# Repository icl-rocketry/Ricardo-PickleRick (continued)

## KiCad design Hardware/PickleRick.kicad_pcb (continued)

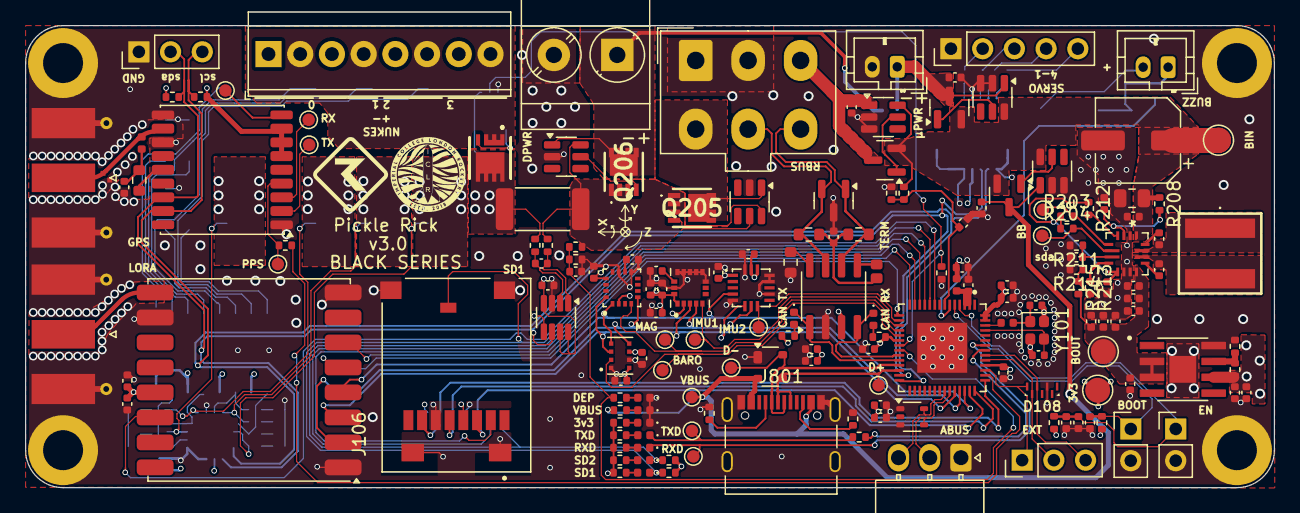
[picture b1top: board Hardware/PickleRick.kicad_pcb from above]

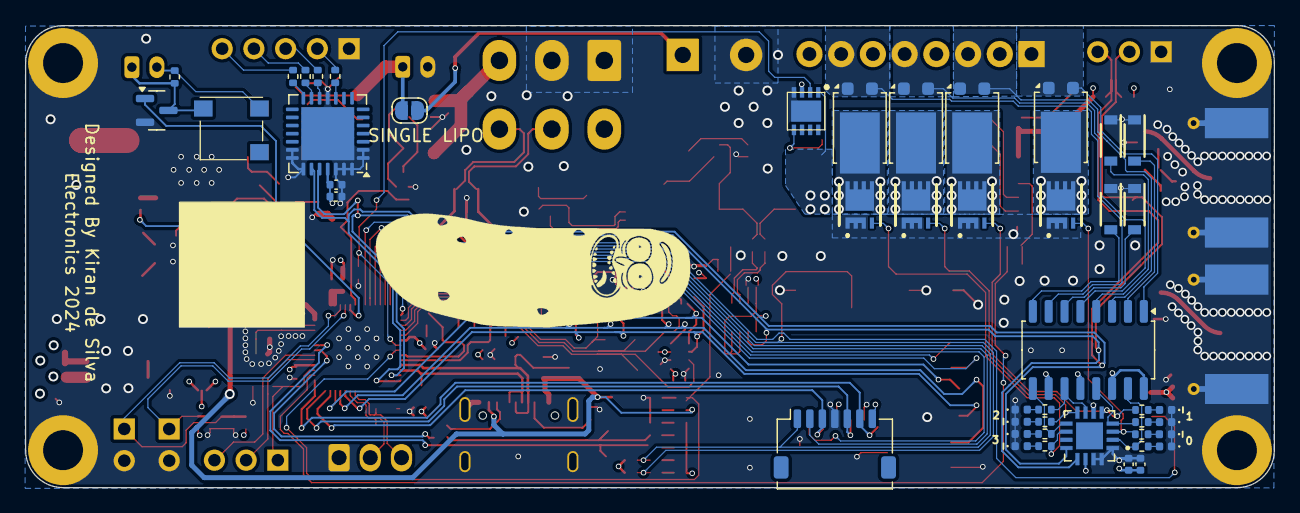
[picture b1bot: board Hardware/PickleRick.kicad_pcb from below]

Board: 6 copper layers, 100.0 x 37.0 mm, 219 parts (45 on the bottom side), 138 nets.

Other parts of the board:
G**: orientation_marker

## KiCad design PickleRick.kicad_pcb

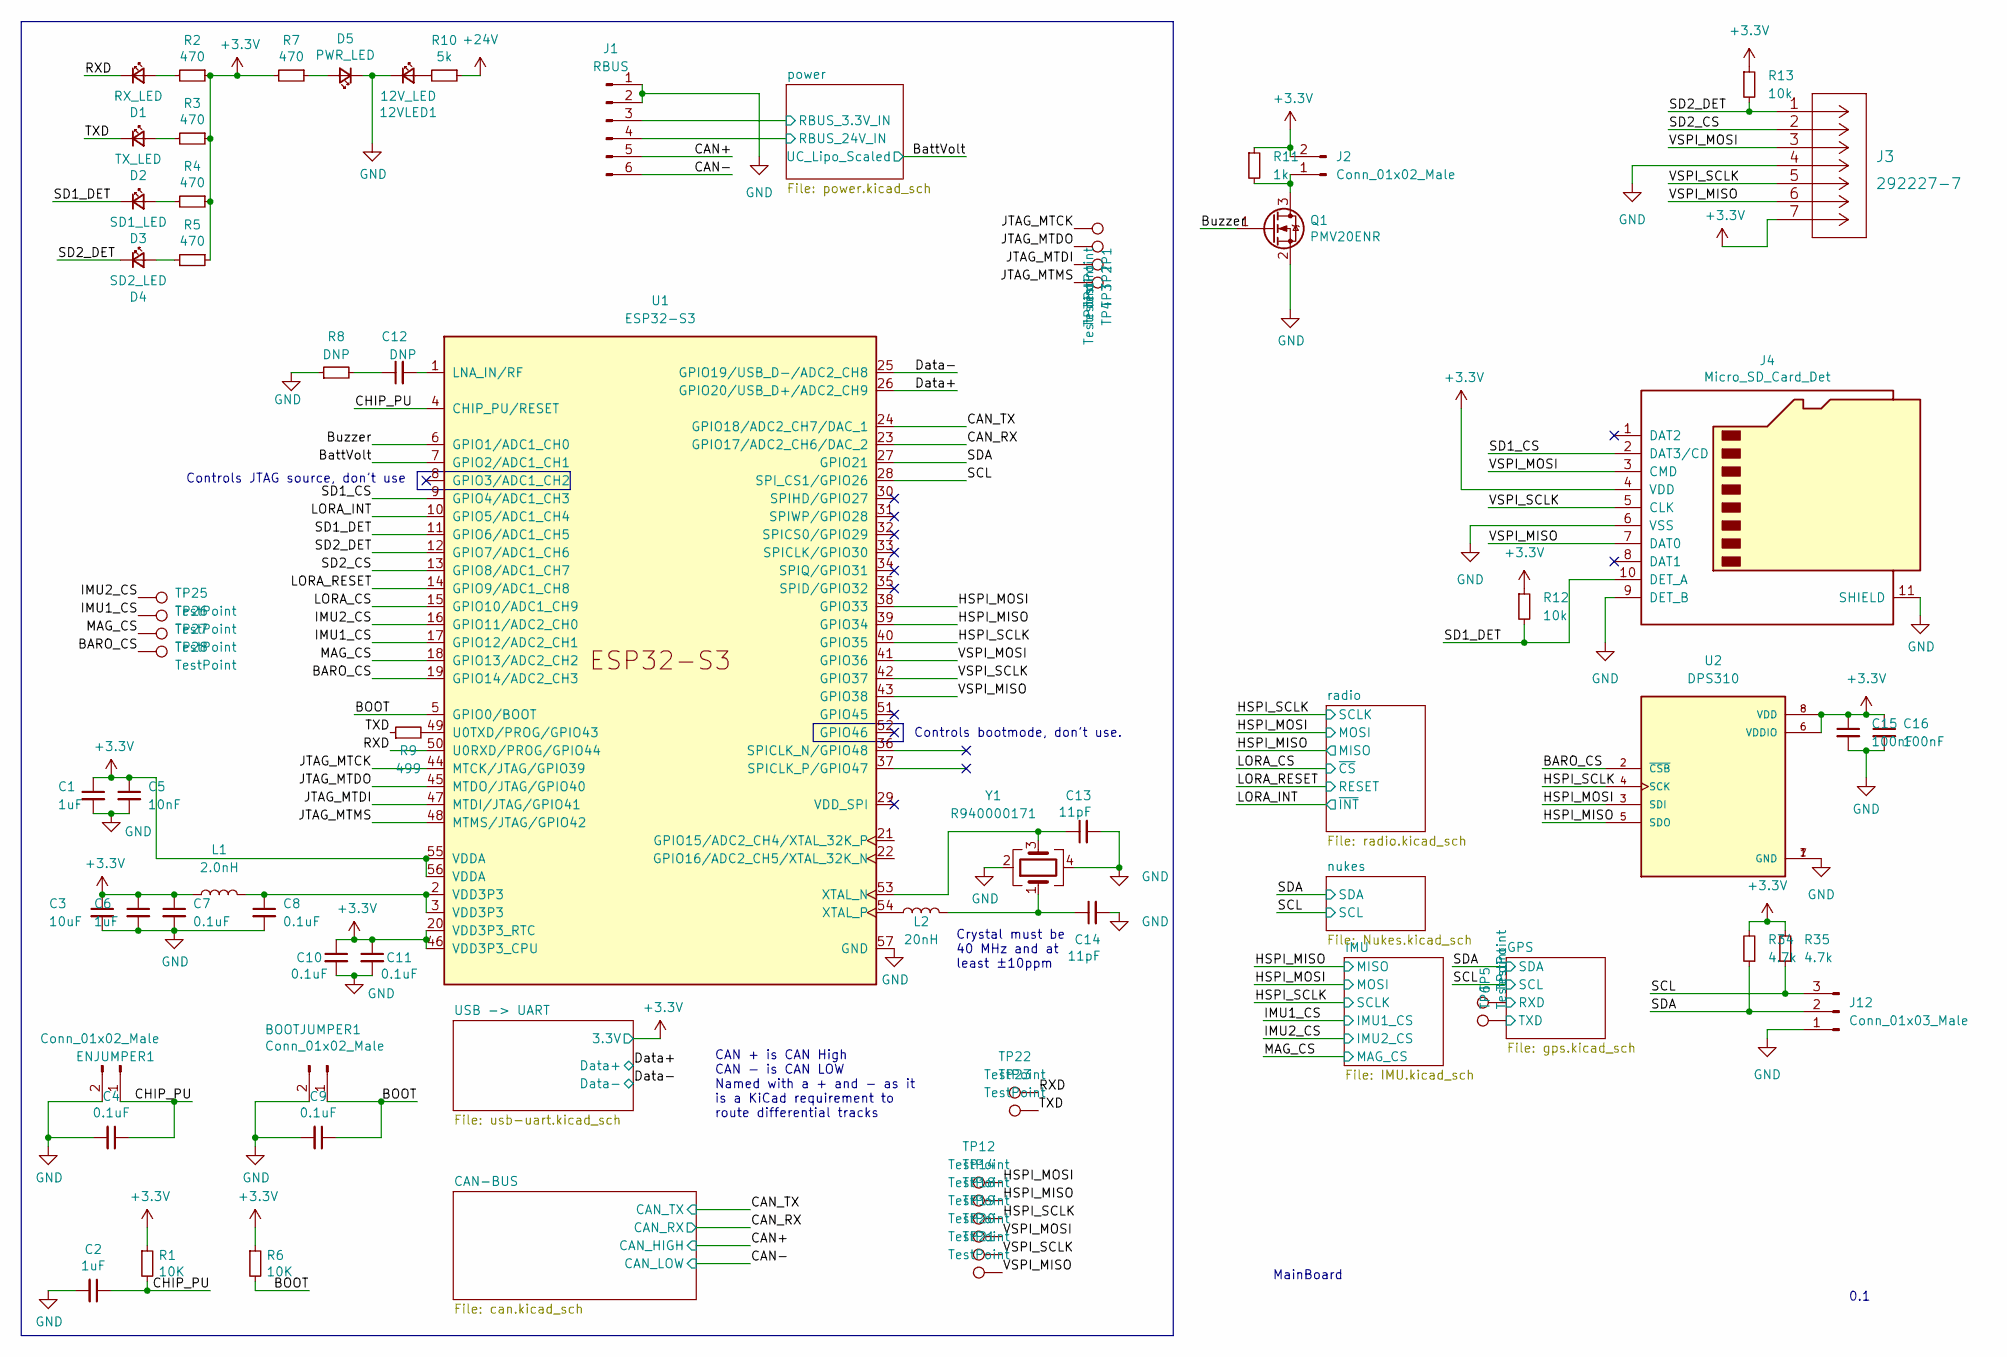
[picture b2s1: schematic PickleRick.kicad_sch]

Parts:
12VLED1: 12V_LED; R_0402_1005Metric
BOOTJUMPER1: Conn_01x02_Male; PinHeader_1x02_P2.54mm_Vertical
C1, C2, C6: 1uF; C_0402_1005Metric
C3: 10uF; C_0402_1005Metric
C4, C7, C8, C9, C10, C11: 0.1uF; C_0402_1005Metric
C5: 10nF; C_0402_1005Metric
C12: DNP; C_0402_1005Metric
C13, C14: 11pF; C_0402_1005Metric
C15, C16: 100nF; C_0402_1005Metric
D1: RX_LED; LED_0402_1005Metric
D2: TX_LED; LED_0402_1005Metric
D3: SD1_LED; LED_0402_1005Metric
D4: SD2_LED; LED_0402_1005Metric
D5: PWR_LED; LED_0402_1005Metric
ENJUMPER1: Conn_01x02_Male; PinHeader_1x02_P2.54mm_Vertical
J1: RBUS; Molex_Mini-Fit_Jr_5566-06A_2x03_P4.20mm_Vertical
J2: Conn_01x02_Male; JST_PH_B2B-PH-K_1x02_P2.00mm_Vertical
J3: 292227-7
J4: Micro_SD_Card_Det; microSD_HC_Hirose_DM3AT-SF-PEJM5
J12: Conn_01x03_Male; PinHeader_1x03_P2.54mm_Vertical
L1: 2.0nH; L_0402_1005Metric
L2: 20nH; L_0402_1005Metric
Q1: PMV20ENR; SOT-23
R1, R6: 10K; R_0402_1005Metric
R2, R3, R4, R5, R7: 470; R_0402_1005Metric
R8: DNP; R_0402_1005Metric
R9: 499; R_0402_1005Metric
R10: 5k; R_0603_1608Metric
R11: 1k; R_0402_1005Metric
R12, R13: 10k; R_0402_1005Metric
R34, R35: 4.7k; R_0402_1005Metric
TP1, TP2, TP3, TP4, TP5, TP6, TP12, TP14, TP18, TP19, TP20, TP21, TP22, TP23, TP25, TP26, TP27, TP28: TestPoint; TestPoint_Pad_D1.0mm
U1: ESP32-S3; QFN40P700X700X90-57N
U2: DPS310; XDCR_DPS310
Y1: R940000171; Crystal_SMD_2016-4Pin_2.0x1.6mm

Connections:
+24V: R10.1; also elsewhere on the board
/BARO_CS: TP28.1, U1.19 (GPIO14/ADC2_CH3), U2.2 (~CSB)
/BOOT: BOOTJUMPER1.1, C9.1, R6.2, U1.5 (GPIO0/BOOT)
/BattVolt: U1.7 (GPIO2/ADC1_CH1); also elsewhere on the board
/Buzzer: Q1.1 (G), U1.6 (GPIO1/ADC1_CH0)
/CAN+: J1.5; also elsewhere on the board
/CAN-: J1.6; also elsewhere on the board
/CAN_RX: U1.23 (GPIO17/ADC2_CH6/DAC_2); also elsewhere on the board
/CAN_TX: U1.24 (GPIO18/ADC2_CH7/DAC_1); also elsewhere on the board
/CHIP_PU: C2.1, C4.1, ENJUMPER1.1, R1.2, U1.4 (CHIP_PU/RESET)
/Data+: U1.26 (GPIO20/USB_D+/ADC2_CH9); also elsewhere on the board
/Data-: U1.25 (GPIO19/USB_D-/ADC2_CH8); also elsewhere on the board
/GPS/RXD: TP5.1; also elsewhere on the board
/GPS/TXD: TP6.1; also elsewhere on the board
/HSPI_MISO: TP14.1, U1.39 (GPIO34), U2.5 (SDO); also elsewhere on the board
/HSPI_MOSI: TP12.1, U1.38 (GPIO33), U2.3 (SDI); also elsewhere on the board
/HSPI_SCLK: TP18.1, U1.40 (GPIO35), U2.4 (SCK); also elsewhere on the board
/IMU1_CS: TP26.1, U1.17 (GPIO12/ADC2_CH1); also elsewhere on the board
/IMU2_CS: TP25.1, U1.16 (GPIO11/ADC2_CH0); also elsewhere on the board
/JTAG_MTCK: TP1.1, U1.44 (MTCK/JTAG/GPIO39)
/JTAG_MTDI: TP3.1, U1.47 (MTDI/JTAG/GPIO41)
/JTAG_MTDO: TP2.1, U1.45 (MTDO/JTAG/GPIO40)
/JTAG_MTMS: TP4.1, U1.48 (MTMS/JTAG/GPIO42)
/LORA_CS: U1.15 (GPIO10/ADC1_CH9); also elsewhere on the board
/LORA_INT: U1.10 (GPIO5/ADC1_CH4); also elsewhere on the board
/LORA_RESET: U1.14 (GPIO9/ADC1_CH8); also elsewhere on the board
/MAG_CS: TP27.1, U1.18 (GPIO13/ADC2_CH2); also elsewhere on the board
/RXD: D1.1 (K), TP22.1, U1.50 (U0RXD/PROG/GPIO44)
/SCL: J12.3, R35.1, U1.28 (SPI_CS1/GPIO26); also elsewhere on the board
/SD1_CS: J4.2 (DAT3/CD), U1.9 (GPIO4/ADC1_CH3)
/SD1_DET: D3.1 (K), J4.10 (DET_A), R12.2, U1.11 (GPIO6/ADC1_CH5)
/SD2_CS: J3.2, U1.13 (GPIO8/ADC1_CH7)
/SD2_DET: D4.1 (K), J3.1, R13.2, U1.12 (GPIO7/ADC1_CH6)
/SDA: J12.2, R34.1, U1.27 (GPIO21); also elsewhere on the board
/TXD: D2.1 (K), R9.1, TP23.1
/VSPI_MISO: J3.6, J4.7 (DAT0), TP21.1, U1.43 (GPIO38)
/VSPI_MOSI: J3.3, J4.3 (CMD), TP19.1, U1.41 (GPIO36)
/VSPI_SCLK: J3.5, J4.5 (CLK), TP20.1, U1.42 (GPIO37)
/power/RBUS_3.3V_IN: J1.3; also elsewhere on the board
/power/RBUS_24V_IN: J1.4; also elsewhere on the board
GND: 12VLED1.1 (K), BOOTJUMPER1.2, C1.2, C2.2, C3.2, C4.2, C5.2, C6.2, C7.2, C8.2, C9.2, C10.2, C11.2, C13.2, C14.2, C15.2, C16.2, D5.1 (K), ENJUMPER1.2, J1.1, J1.2, J3.4, J4.6 (VSS), J4.9 (DET_B), J4.11 (SHIELD), J12.1, Q1.2 (S), R8.1, U1.57 (GND), U2.1 (GND), U2.7 (GND), Y1.2, Y1.4; also elsewhere on the board
unnamed: 12VLED1.2 (A), R10.2
unnamed: C8.1, L1.2, U1.2 (VDD3P3), U1.3 (VDD3P3)
unnamed: C12.1, R8.2
unnamed: C14.1, L2.2, Y1.1
unnamed: D1.2 (A), R2.2
unnamed: D2.2 (A), R3.2
unnamed: D3.2 (A), R4.2
unnamed: D4.2 (A), R5.2
unnamed: D5.2 (A), R7.1
unnamed: J2.1, Q1.3 (D), R11.2
unnamed: C12.2, U1.1 (LNA_IN/RF)
unnamed: R9.2, U1.49 (U0TXD/PROG/GPIO43)
unnamed: C13.1, U1.53 (XTAL_N), Y1.3
unnamed: L2.1, U1.54 (XTAL_P)

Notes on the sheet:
Crystal must be 40 MHz and at least ±10ppm
Controls JTAG source, don't use
CAN + is CAN High CAN - is CAN LOW Named with a + and - as it is a KiCad requirement to route differential tracks
MainBoard
Controls bootmode, don't use.
0.1

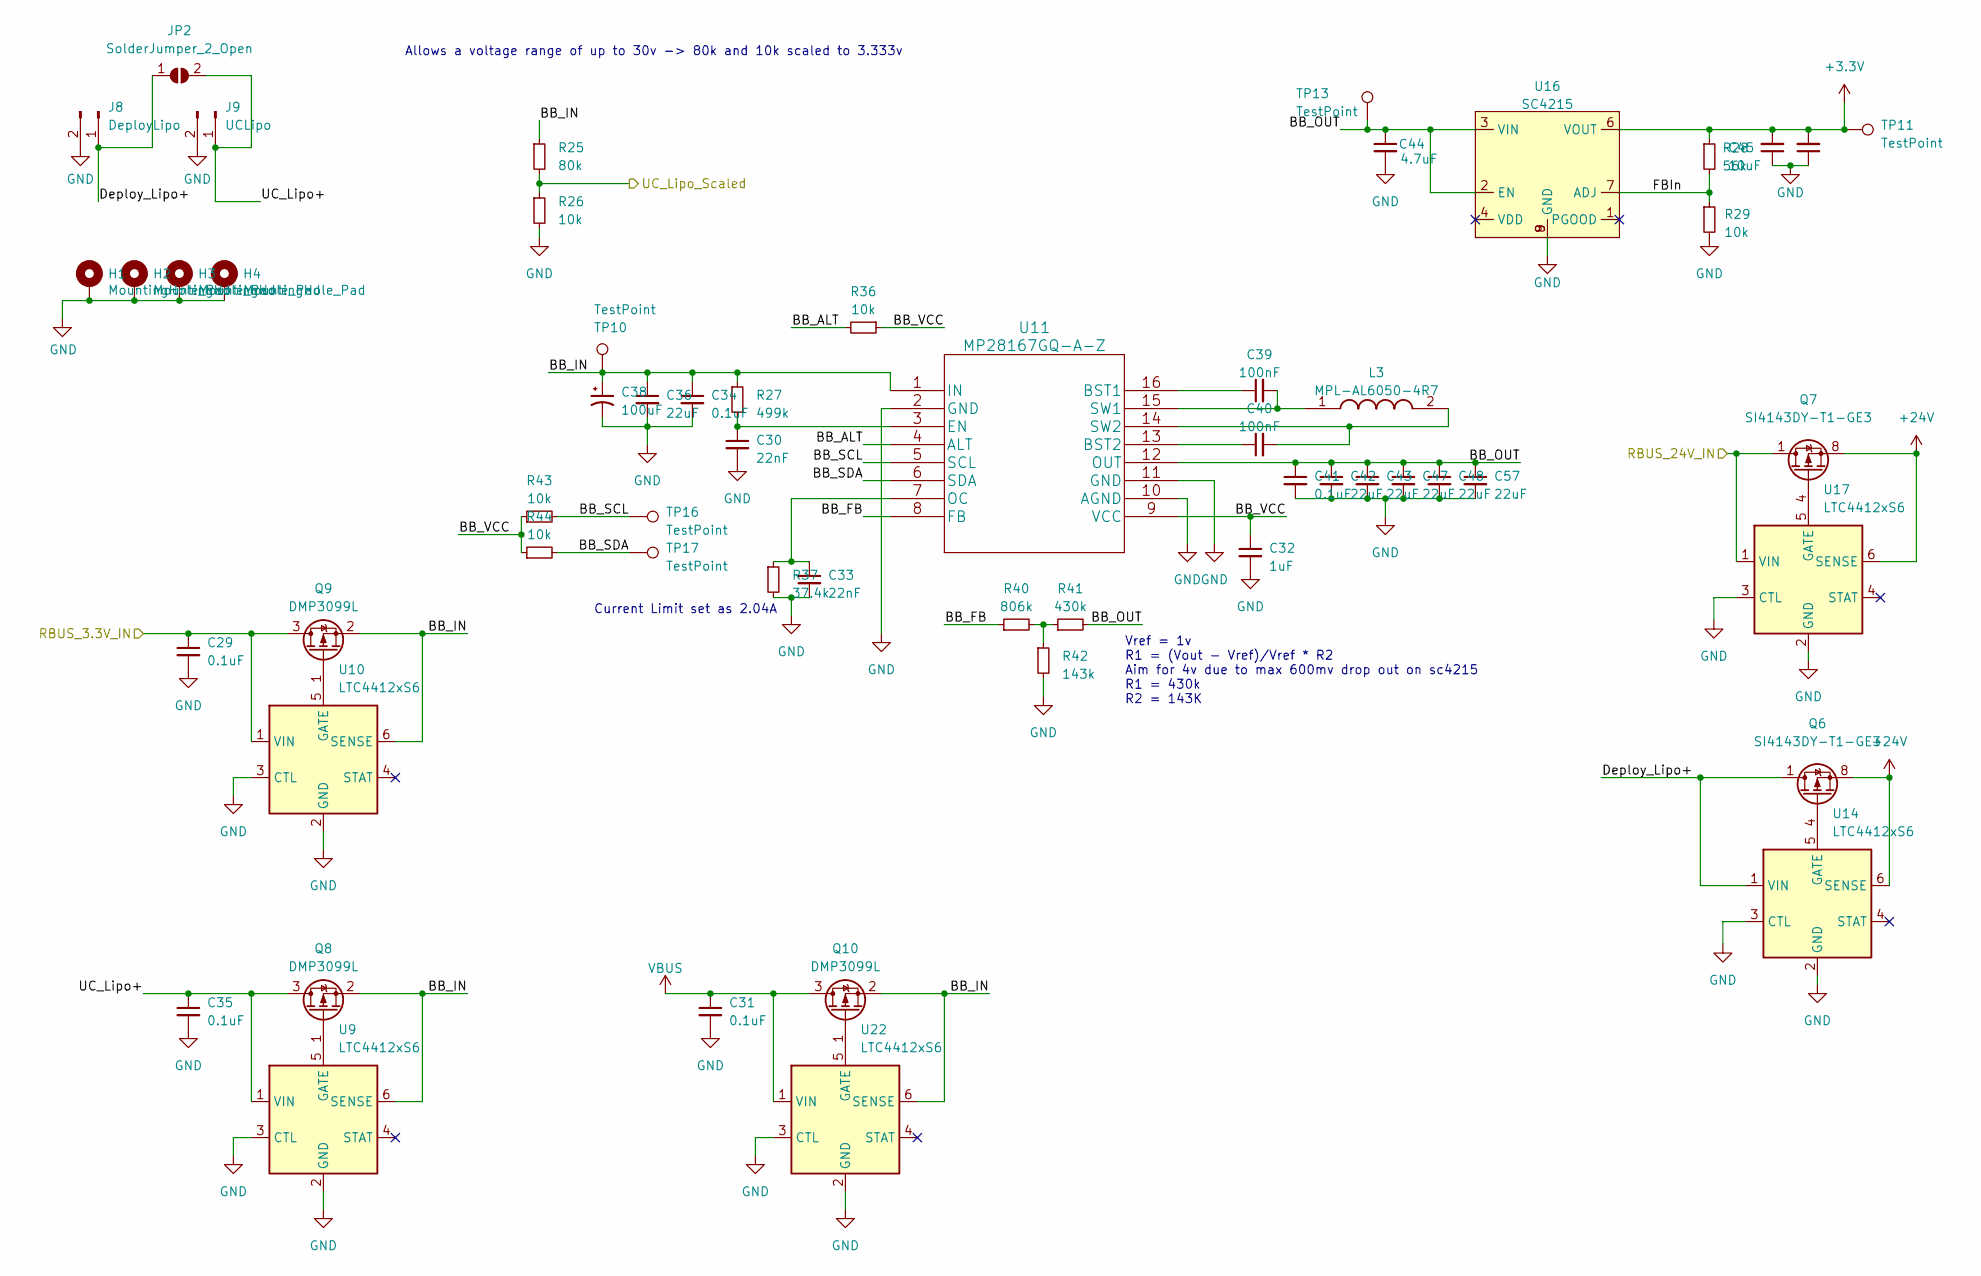
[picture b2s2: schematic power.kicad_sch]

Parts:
C29, C31, C34, C35, C41, C46: 0.1uF; C_0402_1005Metric
C30, C33: 22nF; C_0402_1005Metric
C32: 1uF; C_0402_1005Metric
C36: 22uF; C_0805_2012Metric
C38: 100uF; CP_Elec_6.3x9.9
C39, C40: 100nF; C_0402_1005Metric
C42, C43, C47, C48, C57: 22uF; C_0402_1005Metric
C44: 4.7uF; C_0402_1005Metric
C45: 10uF; C_0402_1005Metric
H1, H2, H3, H4: MountingHole_Pad; MountingHole_3.2mm_M3_DIN965_Pad
J8: DeployLipo; TerminalBlock_Phoenix_MKDS-3-2-5.08_1x02_P5.08mm_Horizontal
J9: UCLipo; JST_PH_B2B-PH-K_1x02_P2.00mm_Vertical
JP2: SolderJumper_2_Open; SolderJumper-2_P1.3mm_Open_RoundedPad1.0x1.5mm
L3: MPL-AL6050-4R7; MPLAL60504R7; Manufacturer_Part_Number MPL-AL6050-4R7; Mouser Part Number 946-MPL-AL6050-4R7
Q6, Q7: SI4143DY-T1-GE3; SOIC-8_3.9x4.9mm_P1.27mm
Q8, Q9, Q10: DMP3099L; SOT-23
R25: 80k; R_0402_1005Metric
R26, R29: 10k; R_0402_1005Metric
R27: 499k; C_0402_1005Metric
R28: 56k; R_0402_1005Metric
R36, R43, R44: 10k; C_0402_1005Metric
R37: 37.4k; C_0402_1005Metric
R40: 806k; C_0402_1005Metric
R41: 430k; C_0402_1005Metric
R42: 143k; C_0402_1005Metric
TP10, TP11, TP13: TestPoint; TestPoint_Pad_D2.0mm
TP16, TP17: TestPoint; TestPoint_Pad_D1.0mm
U9, U10, U14, U17, U22: LTC4412xS6; TSOT-23-6
U11: MP28167GQ-A-Z
U16: SC4215; SOIC127P599X175-9N

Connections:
+24V: Q6.5 (D), Q6.6 (D), Q6.7 (D), Q6.8 (D), Q7.5 (D), Q7.6 (D), Q7.7 (D), Q7.8 (D), U14.6 (SENSE), U17.6 (SENSE); also elsewhere on the board
/BattVolt: R25.2, R26.1; also elsewhere on the board
/power/BB_ALT: R36.2, U11.4 (ALT)
/power/BB_FB: R40.1, U11.8 (FB)
/power/BB_IN: C34.1, C36.1, C38.1, Q8.2 (S), Q9.2 (S), Q10.2 (S), R25.1, R27.1, TP10.1, U9.6 (SENSE), U10.6 (SENSE), U11.1 (IN), U22.6 (SENSE)
/power/BB_OUT: C41.1, C42.1, C43.1, C44.1, C47.1, C48.1, C57.1, R41.2, TP13.1, U11.12 (OUT), U16.2 (EN), U16.3 (VIN)
/power/BB_SCL: R43.2, TP16.1, U11.5 (SCL)
/power/BB_SDA: R44.2, TP17.1, U11.6 (SDA)
/power/BB_VCC: C32.1, R36.1, R43.1, R44.1, U11.9 (VCC)
/power/Deploy_Lipo+: J8.1, JP2.1 (A), Q6.1 (S), Q6.2 (S), Q6.3 (S), U14.1 (VIN)
/power/FBIn: R28.2, R29.1, U16.7 (ADJ)
/power/RBUS_3.3V_IN: C29.1, Q9.3 (D), U10.1 (VIN); also elsewhere on the board
/power/RBUS_24V_IN: Q7.1 (S), Q7.2 (S), Q7.3 (S), U17.1 (VIN); also elsewhere on the board
/power/UC_Lipo+: C35.1, J9.1, JP2.2 (B), Q8.3 (D), U9.1 (VIN)
GND: C29.2, C30.2, C31.2, C32.2, C33.2, C34.2, C35.2, C36.2, C38.2, C41.2, C42.2, C43.2, C44.2, C45.1, C46.1, C47.2, C48.2, C57.2, H1.1, H2.1, H3.1, H4.1, J8.2, J9.2, R26.2, R29.2, R37.2, R42.2, U9.2 (GND), U9.3 (CTL), U10.2 (GND), U10.3 (CTL), U11.2 (GND), U11.10 (AGND), U11.11 (GND), U14.2 (GND), U14.3 (CTL), U16.8 (GND), U16.9 (GND), U17.2 (GND), U17.3 (CTL), U22.2 (GND), U22.3 (CTL); also elsewhere on the board
unnamed: Q6.4 (G), U14.5 (GATE)
unnamed: Q7.4 (G), U17.5 (GATE)
unnamed: Q8.1 (G), U9.5 (GATE)
unnamed: Q9.1 (G), U10.5 (GATE)
unnamed: Q10.1 (G), U22.5 (GATE)
unnamed: R40.2, R41.1, R42.1
unnamed: C39.1, U11.16 (BST1)
unnamed: C40.1, U11.13 (BST2)
unnamed: C30.1, R27.2, U11.3 (EN)
unnamed: C33.1, R37.1, U11.7 (OC)
unnamed: C39.2, L3.1, U11.15 (SW1)
unnamed: C40.2, L3.2, U11.14 (SW2)
VBUS: C31.1, Q10.3 (D), U22.1 (VIN); also elsewhere on the board

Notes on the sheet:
Allows a voltage range of up to 30v -> 80k and 10k scaled to 3.333v
Vref = 1v R1 = (Vout - Vref)/Vref * R2 Aim for 4v due to max 600mv drop out on sc4215 R1 = 430k R2 = 143K
Current Limit set as 2.04A

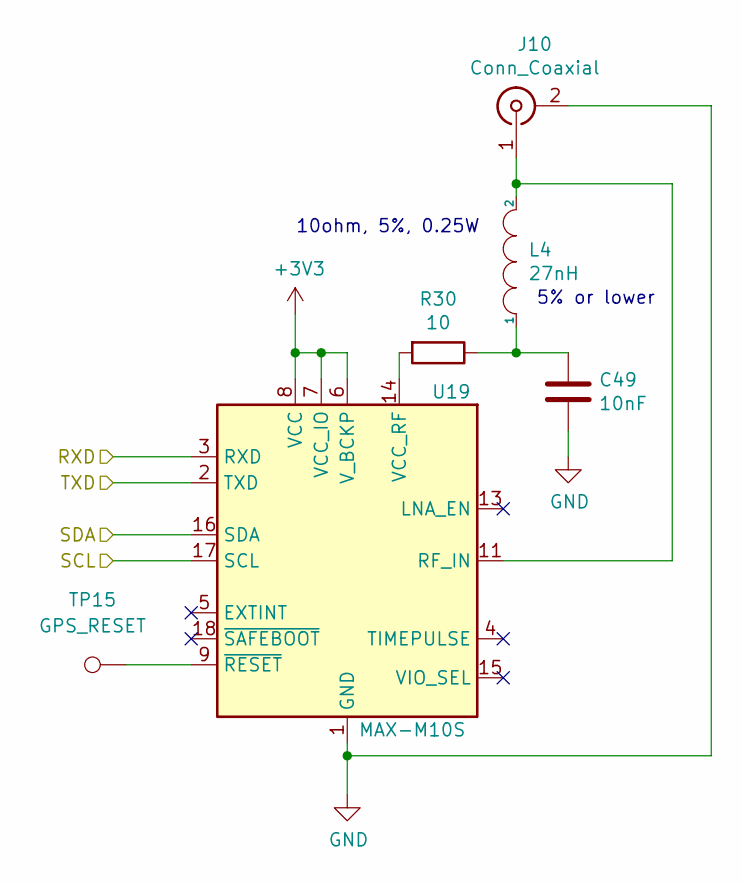
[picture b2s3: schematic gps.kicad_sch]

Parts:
C49: 10nF; C_0402_1005Metric
J10: Conn_Coaxial; SMA_Molex_73251-1153_EdgeMount_Horizontal
L4: 27nH; L_0402_1005Metric; Part LQG15HZ27NH02D
R30: 10; R_0603_1608Metric
TP15: GPS_RESET; TestPoint_Pad_D1.0mm
U19: MAX-M10S; ublox_MAX

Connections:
/GPS/RXD: U19.3 (RXD); also elsewhere on the board
/GPS/TXD: U19.2 (TXD); also elsewhere on the board
/SCL: U19.17 (SCL); also elsewhere on the board
/SDA: U19.16 (SDA); also elsewhere on the board
GND: C49.2, J10.2 (Ext), U19.1 (GND), U19.10 (GND), U19.12 (GND); also elsewhere on the board
unnamed: C49.1, L4.1, R30.1
unnamed: J10.1 (In), L4.2, U19.11 (RF_IN)
unnamed: R30.2, U19.14 (VCC_RF)
unnamed: TP15.1, U19.9 (~RESET)

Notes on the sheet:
5% or lower
10ohm, 5%, 0.25W

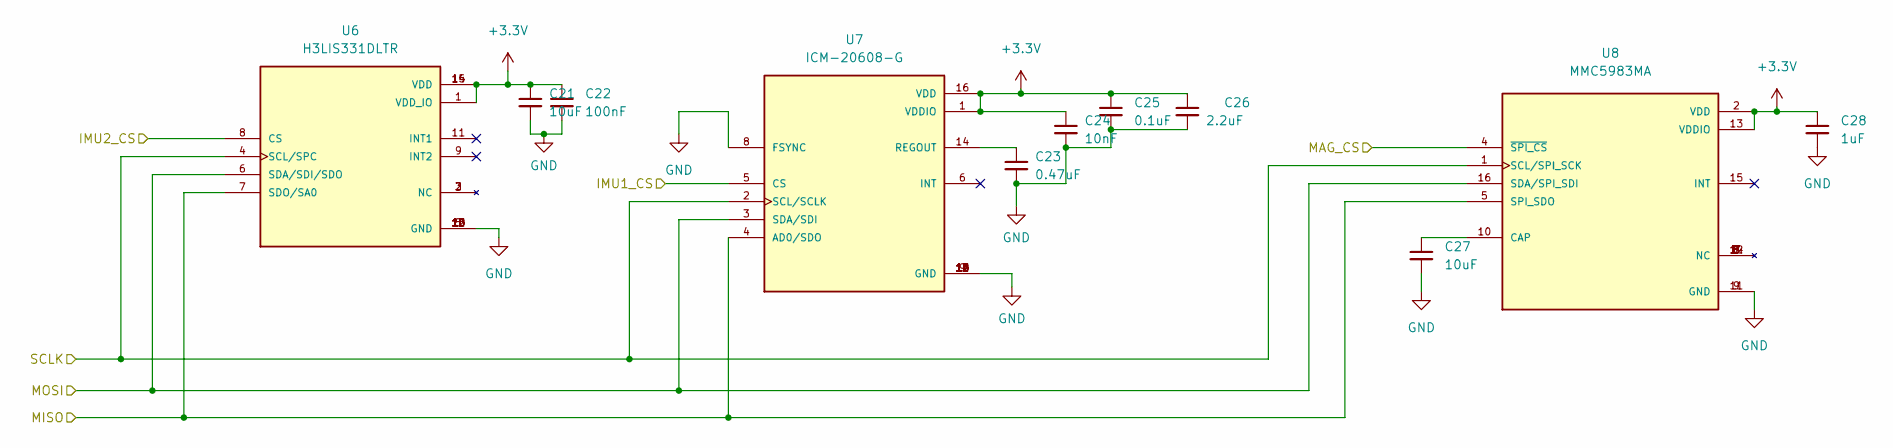
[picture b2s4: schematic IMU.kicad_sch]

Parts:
C21, C27: 10uF; C_0402_1005Metric
C22: 100nF; C_0402_1005Metric
C23: 0.47uF; C_0402_1005Metric
C24: 10nF; C_0402_1005Metric
C25: 0.1uF; C_0402_1005Metric
C26: 2.2uF; C_0402_1005Metric
C28: 1uF; C_0402_1005Metric
U6: H3LIS331DLTR; QFN300X300X100-16N; PARTREV 2
U7: ICM-20608-G; PQFN50P300X300X80-16N; PARTREV 1.0
U8: MMC5983MA; PQFN50P300X300X100-16N; PARTREV A

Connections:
/HSPI_MISO: U6.7 (SDO/SA0), U7.4 (AD0/SDO), U8.5 (SPI_SDO); also elsewhere on the board
/HSPI_MOSI: U6.6 (SDA/SDI/SDO), U7.3 (SDA/SDI), U8.16 (SDA/SPI_SDI); also elsewhere on the board
/HSPI_SCLK: U6.4 (SCL/SPC), U7.2 (SCL/SCLK), U8.1 (SCL/SPI_SCK); also elsewhere on the board
/IMU1_CS: U7.5 (CS); also elsewhere on the board
/IMU2_CS: U6.8 (CS); also elsewhere on the board
/MAG_CS: U8.4 (~SPI_CS); also elsewhere on the board
GND: C21.2, C22.2, C23.2, C24.2, C25.2, C26.2, C27.2, C28.2, U6.5 (GND), U6.10 (GND), U6.12 (GND), U6.13 (GND), U6.16 (GND), U7.8 (FSYNC), U7.9 (GND), U7.10 (GND), U7.11 (GND), U7.12 (GND), U7.13 (GND), U7.15 (GND), U8.9 (GND), U8.11 (GND); also elsewhere on the board
unnamed: C23.1, U7.14 (REGOUT)
unnamed: C27.1, U8.10 (CAP)

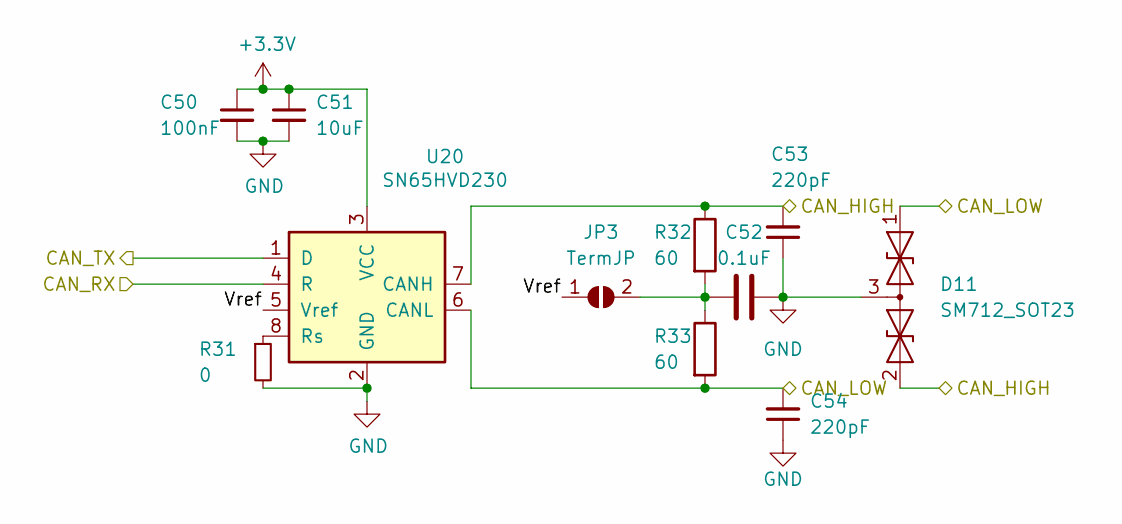
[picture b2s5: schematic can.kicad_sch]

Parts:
C50: 100nF; C_0402_1005Metric
C51: 10uF; C_0402_1005Metric
C52: 0.1uF; C_0402_1005Metric
C53, C54: 220pF; C_0402_1005Metric
D11: SM712_SOT23; SOT-23
JP3: TermJP; SolderJumper-2_P1.3mm_Open_RoundedPad1.0x1.5mm
R31: 0; R_0603_1608Metric
R32, R33: 60; R_0402_1005Metric
U20: SN65HVD230; SOIC-8_3.9x4.9mm_P1.27mm

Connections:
/CAN+: C53.2, D11.2 (A2), R32.1, U20.7 (CANH); also elsewhere on the board
/CAN-: C54.2, D11.1 (A1), R33.2, U20.6 (CANL); also elsewhere on the board
/CAN-BUS/Vref: JP3.1 (A), U20.5 (Vref)
/CAN_RX: U20.4 (R); also elsewhere on the board
/CAN_TX: U20.1 (D); also elsewhere on the board
GND: C50.2, C51.2, C52.2, C53.1, C54.1, D11.3 (common), R31.2, U20.2 (GND); also elsewhere on the board
unnamed: C52.1, JP3.2 (B), R32.2, R33.1
unnamed: R31.1, U20.8 (Rs)

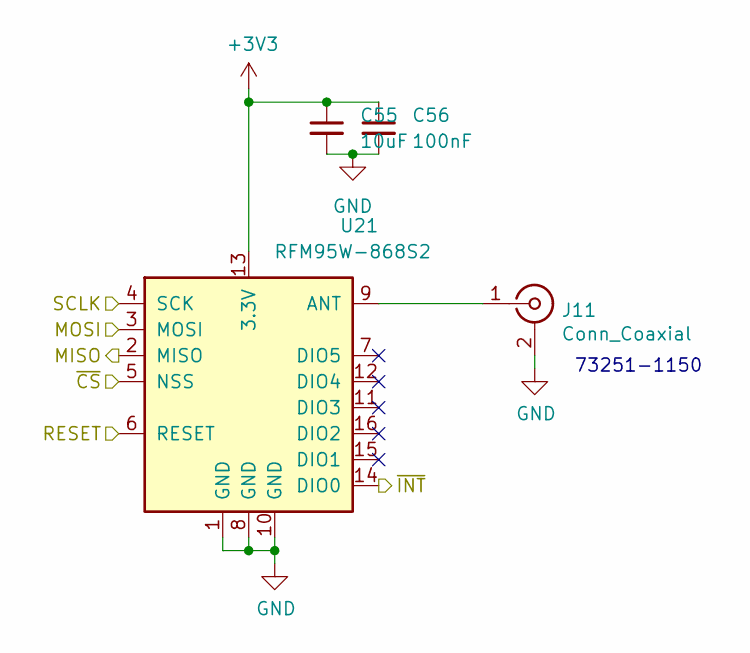
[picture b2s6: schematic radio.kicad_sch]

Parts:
C55: 10uF; C_0402_1005Metric
C56: 100nF; C_0402_1005Metric
J11: Conn_Coaxial; SMA_Molex_73251-1153_EdgeMount_Horizontal
U21: RFM95W-868S2; HOPERF_RFM9XW_SMD

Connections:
/HSPI_MISO: U21.2 (MISO); also elsewhere on the board
/HSPI_MOSI: U21.3 (MOSI); also elsewhere on the board
/HSPI_SCLK: U21.4 (SCK); also elsewhere on the board
/LORA_CS: U21.5 (NSS); also elsewhere on the board
/LORA_INT: U21.14 (DIO0); also elsewhere on the board
/LORA_RESET: U21.6 (RESET); also elsewhere on the board
GND: C55.2, C56.2, J11.2 (Ext), U21.1 (GND), U21.8 (GND), U21.10 (GND); also elsewhere on the board
unnamed: J11.1 (In), U21.9 (ANT)

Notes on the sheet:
73251-1150

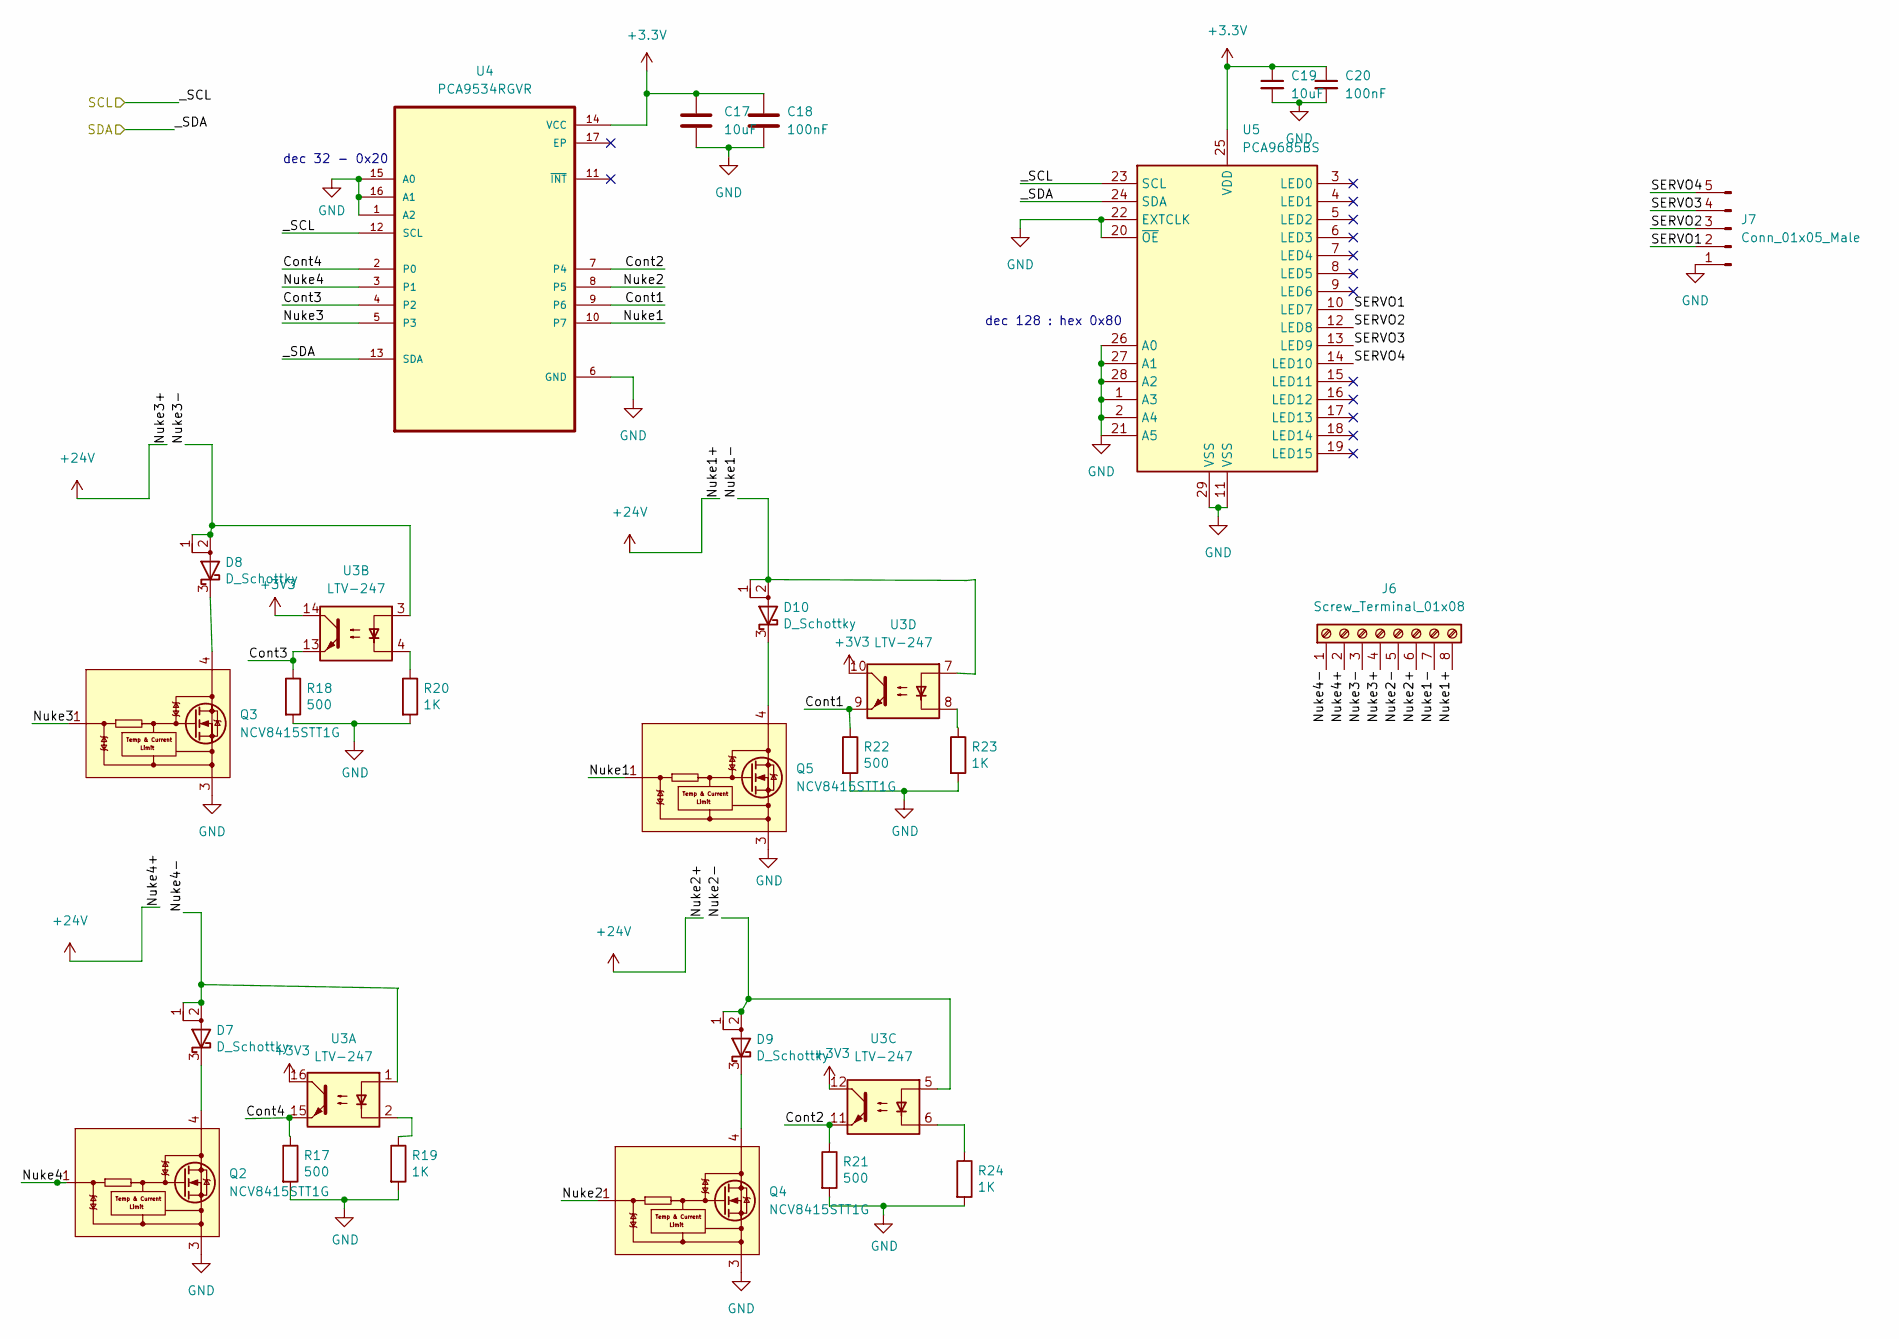
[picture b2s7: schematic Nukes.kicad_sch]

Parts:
C17, C19: 10uF; C_0402_1005Metric
C18, C20: 100nF; C_0402_1005Metric
D7, D8, D9, D10: D_Schottky; TO-277B
J6: Screw_Terminal_01x08; TerminalBlock_TE_282834-8_1x08_P2.54mm_Horizontal
J7: Conn_01x05_Male; PinHeader_1x05_P2.54mm_Vertical
Q2, Q3, Q4, Q5: NCV8415STT1G; SOT-223
R17, R18, R21, R22: 500; R_0402_1005Metric
R19, R20, R23, R24: 1K; R_0603_1608Metric
U3: LTV-247; SOP-16_4.4x10.4mm_P1.27mm
U4: PCA9534RGVR; QFN65P400X400X100-17N
U5: PCA9685BS; QFN-28-1EP_6x6mm_P0.65mm_EP4.25x4.25mm

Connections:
+24V: J6.2, J6.4, J6.6, J6.8; also elsewhere on the board
/SCL: U4.12 (SCL), U5.23 (SCL); also elsewhere on the board
/SDA: U4.13 (SDA), U5.24 (SDA); also elsewhere on the board
/nukes/Cont1: R22.1, U3.9, U4.9 (P6)
/nukes/Cont2: R21.1, U3.11, U4.7 (P4)
/nukes/Cont3: R18.1, U3.13, U4.4 (P2)
/nukes/Cont4: R17.1, U3.15, U4.2 (P0)
/nukes/Nuke1: Q5.1 (G), U4.10 (P7)
/nukes/Nuke1-: D10.1 (A), D10.2 (A), J6.7, U3.7
/nukes/Nuke2: Q4.1 (G), U4.8 (P5)
/nukes/Nuke2-: D9.1 (A), D9.2 (A), J6.5, U3.5
/nukes/Nuke3: Q3.1 (G), U4.5 (P3)
/nukes/Nuke3-: D8.1 (A), D8.2 (A), J6.3, U3.3
/nukes/Nuke4: Q2.1 (G), U4.3 (P1)
/nukes/Nuke4-: D7.1 (A), D7.2 (A), J6.1, U3.1
/nukes/SERVO1: J7.2, U5.10 (LED7)
/nukes/SERVO2: J7.3, U5.12 (LED8)
/nukes/SERVO3: J7.4, U5.13 (LED9)
/nukes/SERVO4: J7.5, U5.14 (LED10)
GND: C17.2, C18.2, C19.2, C20.2, J7.1, Q2.3 (S), Q3.3 (S), Q4.3 (S), Q5.3 (S), R17.2, R18.2, R19.2, R20.2, R21.2, R22.2, R23.2, R24.2, U4.1 (A2), U4.6 (GND), U4.15 (A0), U4.16 (A1), U5.1 (A3), U5.2 (A4), U5.11 (VSS), U5.20 (~OE), U5.21 (A5), U5.22 (EXTCLK), U5.26 (A0), U5.27 (A1), U5.28 (A2), U5.29 (VSS); also elsewhere on the board
unnamed: D7.3 (K), Q2.2 (D), Q2.4 (D)
unnamed: D8.3 (K), Q3.2 (D), Q3.4 (D)
unnamed: D9.3 (K), Q4.2 (D), Q4.4 (D)
unnamed: D10.3 (K), Q5.2 (D), Q5.4 (D)
unnamed: R19.1, U3.2
unnamed: R20.1, U3.4
unnamed: R23.1, U3.8
unnamed: R24.1, U3.6

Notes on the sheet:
dec 32 - 0x20
dec 128 : hex 0x80

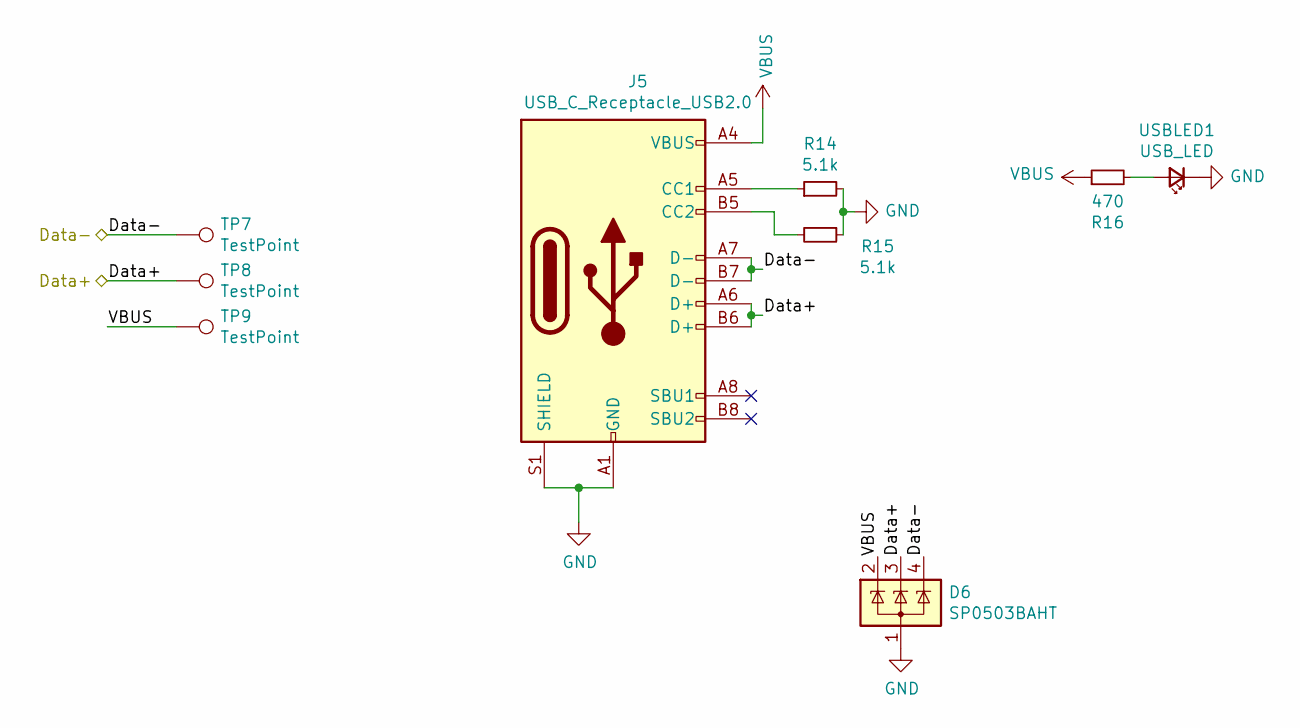
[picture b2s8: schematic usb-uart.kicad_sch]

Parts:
D6: SP0503BAHT; SOT-143
J5: USB_C_Receptacle_USB2.0; USB_C_Receptacle_Palconn_UTC16-G
R14, R15: 5.1k; R_0402_1005Metric
R16: 470; R_0402_1005Metric
TP7, TP8, TP9: TestPoint; TestPoint_Pad_D1.0mm
USBLED1: USB_LED; R_0402_1005Metric

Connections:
/Data+: D6.3 (K), J5.A6 (D+), J5.B6 (D+), TP8.1; also elsewhere on the board
/Data-: D6.4 (K), J5.A7 (D-), J5.B7 (D-), TP7.1; also elsewhere on the board
GND: D6.1 (A), J5.A1 (GND), J5.A12 (GND), J5.B1 (GND), J5.B12 (GND), J5.S1 (SHIELD), R14.2, R15.1, USBLED1.1 (K); also elsewhere on the board
unnamed: J5.A5 (CC1), R14.1
unnamed: J5.B5 (CC2), R15.2
unnamed: R16.2, USBLED1.2 (A)
VBUS: D6.2 (K), J5.A4 (VBUS), J5.A9 (VBUS), J5.B4 (VBUS), J5.B9 (VBUS), R16.1, TP9.1; also elsewhere on the board

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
